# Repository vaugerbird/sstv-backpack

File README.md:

# sstv-backpack
## A ESP32-CAM SSTV backpack for the Baofeng UV-5R and others!

## Project Description
### Turn your HT into a point-and-shoot camera!
This project relies on using an ESP32 connected to a handheld transceiver to send SSTV (Slow Scan TeleVision) images. Any combination of HT and ESP32-CAM can send a picture, but the hardware in this repository is specifically designed to work!

To decode the images, another radio must be used and connected to any device that can run a decoder program. I personally use MMSSTV on my PC with a USB soundcard, or my phone running Robot36 and listening to the radio with the microphone. 

Here's some questions I've been asked in the past:
* **Why?**
    * This is a term project that I created for my college ARC that I'm the president of! We are currently assembling v1.1 and we plan on using the completed projects to do a SSTV scavenger hunt. This consists of a list of things to take pictures of around campus, where the hunter will take a picture of the required object, send the image back to the control room (clubroom), and the point will be awarded to the hunter/team!
* **How does this work?**
    * In short, the ESP32-CAM captures a frame, converts the image into the appropriate encoded audio for SSTV, keys the PTT on the HT, and plays the audio through the microphone port. The specifics of the encoding process are somewhat black magic to me as I didn't create the underlying code, but as far as I understand, the encoding is done by applying a few math functions to the pixels stored in the framebuffer, and converted into audio.

## Hardware Revisions
I currently have 2 hardware revisions available, with a 3rd planned: 
1. v1.0:
    * Mostly through-hole and completely hand-solderable
    * Simplest version with only a voltage regulator circuit, PTT circuit, 2 switches, a buzzer, and the ESP32-CAM
    * Requires external board for flashing and a serial monitor
2. v1.1: 
    * 2 sub-versions:
        * v1.1.1: CH340C version, uses the CH340C for USB-to-UART and has CC resistors for full USB type C compatibility.
        * v1.1.0: FT231XS version, uses the FTDI FT231XS for USB-to-UART and does **not** have CC resistors. I don't recommend this version for many reasons, unless it is difficult to get the CH340C. 
    * Still mostly through-hole and hand-solderable, albeit with some fine-pitch components like the USB-to-UART chip.
    * Retains all the same functionality of v1.0, but adds a USB-to-Serial chip for flashing and a serial monitor.
    * The board is quite cramped and may be hard to work with.
3. v1.2 (WIP):
    * Switch to a mostly top-mounted SMD design, while still being hand-solderable
    * Retain all features of the v1.1 board
    * Maybe add battery charging circuitry?

## Assembly Instructions
### Better (printable) instructions coming soon!
1. Upload your desired [Gerber](./hardware/gerbers/) file to your favorite PCB manufacturer. I recommend OSHPark for US-made, decent-priced priced small-batch PCBs. JLCPCB or PCBWay are both great for cheap, high quality PCBs, if you don't mind waiting.

2. Order the required parts using the proper BOM for [v1.0](./hardware/v1.0/sstv-backpack-v1.0.1.csv) or [v1.1](./hardware/v1.1/sstv-backpack-v1.1.1.csv) from your favorite parts supplier.

3. Once all parts arrive, assemble the board. There isn't much of a technique to it, just start with the lowest profile parts first like the diodes, resistors, and chips, and work your way up.

4. Once the board is complete, print the case using one of the included [STLs](./hardware/case). Currently, the Baofeng UV-5R is the only supported radio, but the Inventor 2025 and STEP files are included, and help with additional radio models is always appreciated!

    * I used the standard settings (0.2mm) on my print, with supports on, and the case interior facing the build plate.

    * The case requires these additional parts:
        * 4 - M3 brass het set inserts
        * 4 - M3 x 6mm screws (preferably hex head)
        * 4 - M2 x 4mm screws
        * 1 - Radio cable (I just cut the end off of a cheap Baofeng speaker-mic, it was cheaper than using an unterminated cable.)

5. After you have the hardware assembled, the next thing to do is upload the code!

## Programming Instructions
1. Ensure that you have this link added to the 3rd party boards section of the Arduino IDE (Found under File -> Preferences -> Additional board manager URLs):
```
https://dl.espressif.com/dl/package_esp32_index.json
```

2. From the board manager, install the newest version of the ESP32 board definitions.

3. Set the board model to "AI Thinker ESP32-CAM" and select the appropriate COM port.

4. Change the text options on lines 37 and 38 of [sstv-backpack.ino](./code/sstv-backpack.ino) to reflect your callsign and desired splash text.
    * The color of the top and bottom text can be changed with the definitions in lines 24-31. 

5. Uncomment line 21 ```#define USE_FLASH``` if you want to use the flash LED (Turns on a high intensity white LED on when framegrabbing).

6. At line 447, set `1 = HIGH` or `0 = LOW` properly reflect your CAPT_BTN wiring (GND for LOW, or +3.3V for HIGH)

7. Between line 452-456, choose the correct button pull-up/pull-down configuration. The button is set to pull-up by default to mirror the PCBs. (Button connects to GND when pressed)

8. Inside the "camera.h" file you can choose between two profiles, DAYLIGHT and HOME. Feel free to modify settings to best suit your case. 
	* Notes from IU5HKU:
		* Keep in mind that this cheap sensor struggles a lot in poor light scenarios, so don't expect a picture like your Fujifilm camera.
		* A quick search online can lead you towards the proper settings values you need.

9. All the board settings can be left alone except for selecting the correct COM port.

10. Upload the code!

## Contributors
 A huge thank you to our contributors for this project! I'm pretty bad with code so all help is greatly appreciated!

 * [IU5HKU / Marco](https://github.com/IU5HKU) - Updated the code to work with the newest version of the ESP32 board definition and improved the readability/usability of the code!
 * [IU5HKU / Marco](https://github.com/IU5HKU) - Updated the code to work with deepsleep/wakeup ESP32 functions (maximize battery life).

## Licensing
* The [main program](./code/sstv-backpack.ino) and [supporting libraries](./code/) are licensed as CC BY-NC-SA 4.0 and are based on the program/libraries from [desafioinventor](https://www.instructables.com/SSTV-Capsule-V2-for-High-Altitude-Balloons/) on Instructables. 
* The case design is roughly based on [this design](https://www.thingiverse.com/thing:5270394) by HStakhiv on [Thingiverse](https://www.thingiverse.com/hstakhiv/designs). The original is licensed under CC BY. My case design falls under the GPL-2.0 license.
* The remaining contents of this repository are designed by me (and contributors!), and are licensed under the GPL-2.0 license.

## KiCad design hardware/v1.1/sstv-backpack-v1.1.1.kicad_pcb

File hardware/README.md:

# Hardware
## Currently there are 3 revisions:
* v1.0(.1)
    * Simplest version
    * The board only acts as a voltage regulator, PTT circuit, and carrier for the major parts
* v1.1
    * More complex
    * The board contains the voltage regulator circuit, USB flashing circuit, and PTT circuit
* v1.2
    * Same complexity as v1.1, contains mostly SMD parts

## HW Issues
* v1.0(.1):
    * This board is incapable of flashing the ESP32 or using serial monitor as there is no USB-to-UART chip present. Flashing has to be done with a dedicated programmer and debugging is very difficult. 
* v1.1.0:
    * ~~No CC resistors are present (or really possible) for the USB-C port. This is due to physical restraints of through-hole components, and means the board will not receive power from a USB-C to USB-C cable.~~ Fixed with v1.1.1
    * ~~Powering the board from the radio and connecting USB data is possible, and won't break anything as power is diode-protected, but is not recommended.~~ Fixed with v1.1.1
* v1.2:
    * No issues have been found; this revision of the board has not yet been tested.

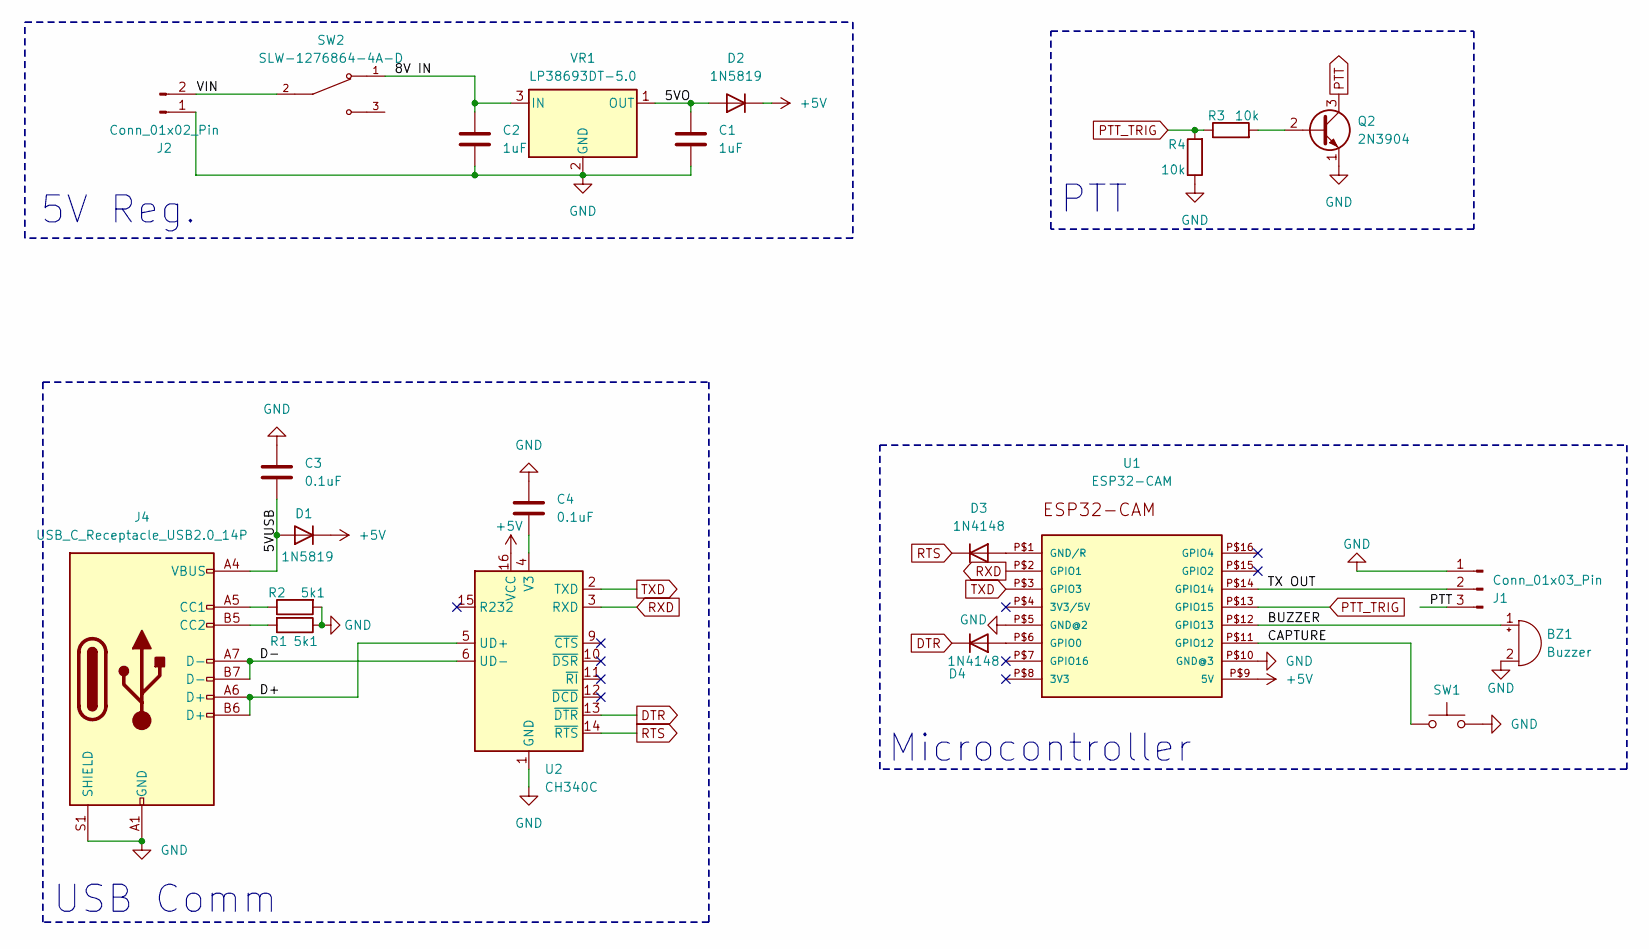
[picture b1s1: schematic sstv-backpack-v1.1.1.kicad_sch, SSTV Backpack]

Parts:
BZ1: Buzzer; Buzzer_TDK_PS1240P02BT_D12.2mm_H6.5mm
C1, C2: 1uF; C_Disc_D3.4mm_W2.1mm_P2.50mm
C3, C4: 0.1uF; C_Disc_D3.4mm_W2.1mm_P2.50mm
D1, D2: 1N5819; D_DO-41_SOD81_P7.62mm_Horizontal
D3, D4: 1N4148; D_DO-41_SOD81_P7.62mm_Horizontal
J1: Conn_01x03_Pin; PinHeader_1x03_P2.54mm_Vertical
J2: Conn_01x02_Pin; PinHeader_1x02_P2.54mm_Vertical
J4: USB_C_Receptacle_USB2.0_14P; USB_C_Receptacle_GCT_USB4085
Q2: 2N3904; TO-92_Inline
R1, R2: 5k1; R_Axial_DIN0207_L6.3mm_D2.5mm_P7.62mm_Horizontal
R3, R4: 10k; R_Axial_DIN0207_L6.3mm_D2.5mm_P7.62mm_Horizontal
SW1: SW_Push
SW2: SLW-1276864-4A-D; SW_SLW-1276864-4A-D; PARTREV 1.01
U1: ESP32-CAM
U2: CH340C; SOIC-16_3.9x9.9mm_P1.27mm
VR1: LP38693DT-5.0; TO-252-2

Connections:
+5V: D1.1 (K), D2.1 (K), U1.P$9 (5V), U2.16 (VCC)
/5VO: C1.1, D2.2 (A), VR1.1 (OUT)
/5VUSB: C3.2, D1.2 (A), J4.A4 (VBUS), J4.A9 (VBUS), J4.B4 (VBUS), J4.B9 (VBUS)
/8V IN: C2.1, SW2.1, VR1.3 (IN)
/BUZZER: BZ1.1 (+), U1.P$12 (GPIO13)
/CAPTURE: SW1.1, U1.P$11 (GPIO12)
/D+: J4.A6 (D+), J4.B6 (D+), U2.5 (UD+)
/D-: J4.A7 (D-), J4.B7 (D-), U2.6 (UD-)
/TX OUT: J1.2, U1.P$14 (GPIO14)
/VIN: J2.2, SW2.2
DTR: D4.1 (K), U2.13 (~DTR)
GND: BZ1.2 (-), C1.2, C2.2, C3.1, C4.1, J1.1, J2.1, J4.A1 (GND), J4.A12 (GND), J4.B1 (GND), J4.B12 (GND), J4.S1 (SHIELD), Q2.1 (E), R1.1, R2.2, R4.1, SW1.2, U1.P$5 (GND@2), U1.P$10 (GND@3), U2.1 (GND), VR1.2 (GND)
unnamed: D3.2 (A), U1.P$1 (GND/R)
unnamed: D4.2 (A), U1.P$6 (GPIO0)
unnamed: J4.A5 (CC1), R2.1
unnamed: J4.B5 (CC2), R1.2
unnamed: Q2.2 (B), R3.2
unnamed: C4.2, U2.4 (V3)
PTT: J1.3, Q2.3 (C)
PTT_TRIG: R3.1, R4.2, U1.P$13 (GPIO15)
RTS: D3.1 (K), U2.14 (~RTS)
RXD: U1.P$2 (GPIO1), U2.3 (RXD)
TXD: U1.P$3 (GPIO3), U2.2 (TXD)

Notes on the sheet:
5V Reg.
Microcontroller
USB Comm
PTT

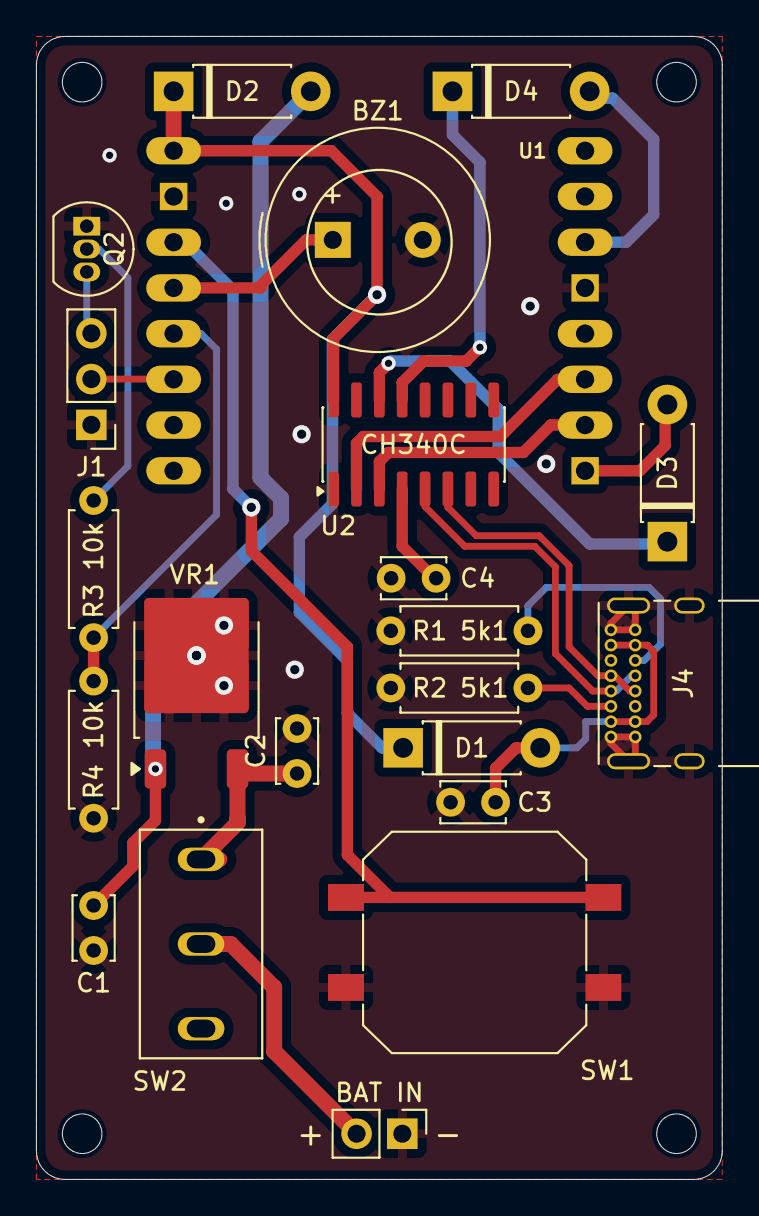
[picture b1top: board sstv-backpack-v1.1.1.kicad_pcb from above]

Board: 2 copper layers, 38.1 x 63.5 mm, 22 parts (0 on the bottom side), 23 nets.

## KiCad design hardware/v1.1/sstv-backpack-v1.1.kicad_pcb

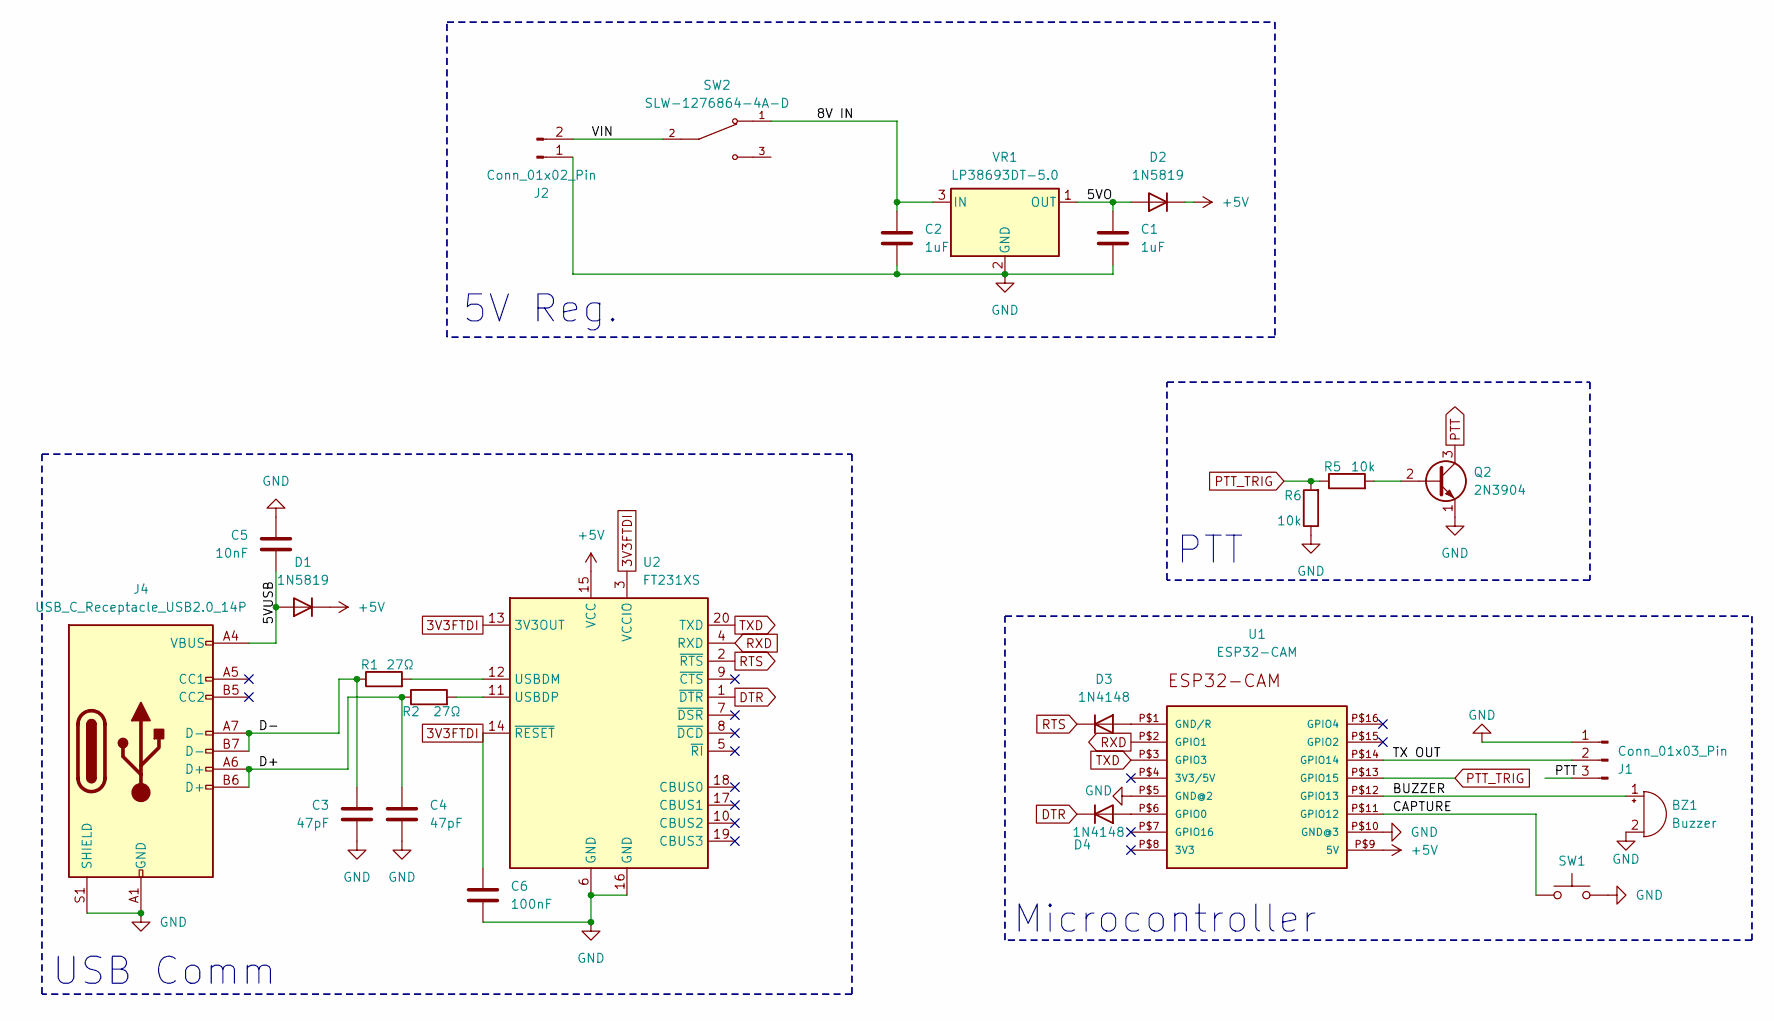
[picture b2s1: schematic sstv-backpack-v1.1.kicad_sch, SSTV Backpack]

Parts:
BZ1: Buzzer; Buzzer_TDK_PS1240P02BT_D12.2mm_H6.5mm
C1, C2: 1uF; C_Disc_D3.4mm_W2.1mm_P2.50mm
C3, C4: 47pF; C_Disc_D4.7mm_W2.5mm_P5.00mm
C5: 10nF; C_Disc_D4.7mm_W2.5mm_P5.00mm
C6: 100nF; C_Disc_D4.7mm_W2.5mm_P5.00mm
D1, D2: 1N5819; D_DO-41_SOD81_P7.62mm_Horizontal
D3, D4: 1N4148; D_DO-41_SOD81_P7.62mm_Horizontal
J1: Conn_01x03_Pin; PinHeader_1x03_P2.54mm_Vertical
J2: Conn_01x02_Pin; PinHeader_1x02_P2.54mm_Vertical
J4: USB_C_Receptacle_USB2.0_14P; USB_C_Receptacle_GCT_USB4085
Q2: 2N3904; TO-92_Inline
R1, R2: 27Ω; R_Axial_DIN0207_L6.3mm_D2.5mm_P7.62mm_Horizontal
R5, R6: 10k; R_Axial_DIN0207_L6.3mm_D2.5mm_P7.62mm_Horizontal
SW1: SW_Push
SW2: SLW-1276864-4A-D; SW_SLW-1276864-4A-D; PARTREV 1.01
U1: ESP32-CAM
U2: FT231XS; SSOP-20_3.9x8.7mm_P0.635mm
VR1: LP38693DT-5.0; TO-252-2

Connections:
3V3FTDI: C6.1, U2.3 (VCCIO), U2.13 (3V3OUT), U2.14 (~RESET)
+5V: D1.1 (K), D2.1 (K), U1.P$9 (5V), U2.15 (VCC)
/5VO: C1.1, D2.2 (A), VR1.1 (OUT)
/5VUSB: C5.2, D1.2 (A), J4.A4 (VBUS), J4.A9 (VBUS), J4.B4 (VBUS), J4.B9 (VBUS)
/8V IN: C2.1, SW2.1, VR1.3 (IN)
/BUZZER: BZ1.1 (+), U1.P$12 (GPIO13)
/CAPTURE: SW1.1, U1.P$11 (GPIO12)
/D+: C4.1, J4.A6 (D+), J4.B6 (D+), R2.1
/D-: C3.1, J4.A7 (D-), J4.B7 (D-), R1.1
/TX OUT: J1.2, U1.P$14 (GPIO14)
/VIN: J2.2, SW2.2
DTR: D4.1 (K), U2.1 (~DTR)
GND: BZ1.2 (-), C1.2, C2.2, C3.2, C4.2, C5.1, C6.2, J1.1, J2.1, J4.A1 (GND), J4.A12 (GND), J4.B1 (GND), J4.B12 (GND), J4.S1 (SHIELD), Q2.1 (E), R6.1, SW1.2, U1.P$5 (GND@2), U1.P$10 (GND@3), U2.6 (GND), U2.16 (GND), VR1.2 (GND)
unnamed: D3.2 (A), U1.P$1 (GND/R)
unnamed: D4.2 (A), U1.P$6 (GPIO0)
unnamed: Q2.2 (B), R5.2
unnamed: R1.2, U2.12 (USBDM)
unnamed: R2.2, U2.11 (USBDP)
PTT: J1.3, Q2.3 (C)
PTT_TRIG: R5.1, R6.2, U1.P$13 (GPIO15)
RTS: D3.1 (K), U2.2 (~RTS)
RXD: U1.P$2 (GPIO1), U2.4 (RXD)
TXD: U1.P$3 (GPIO3), U2.20 (TXD)

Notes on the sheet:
5V Reg.
Microcontroller
USB Comm
PTT

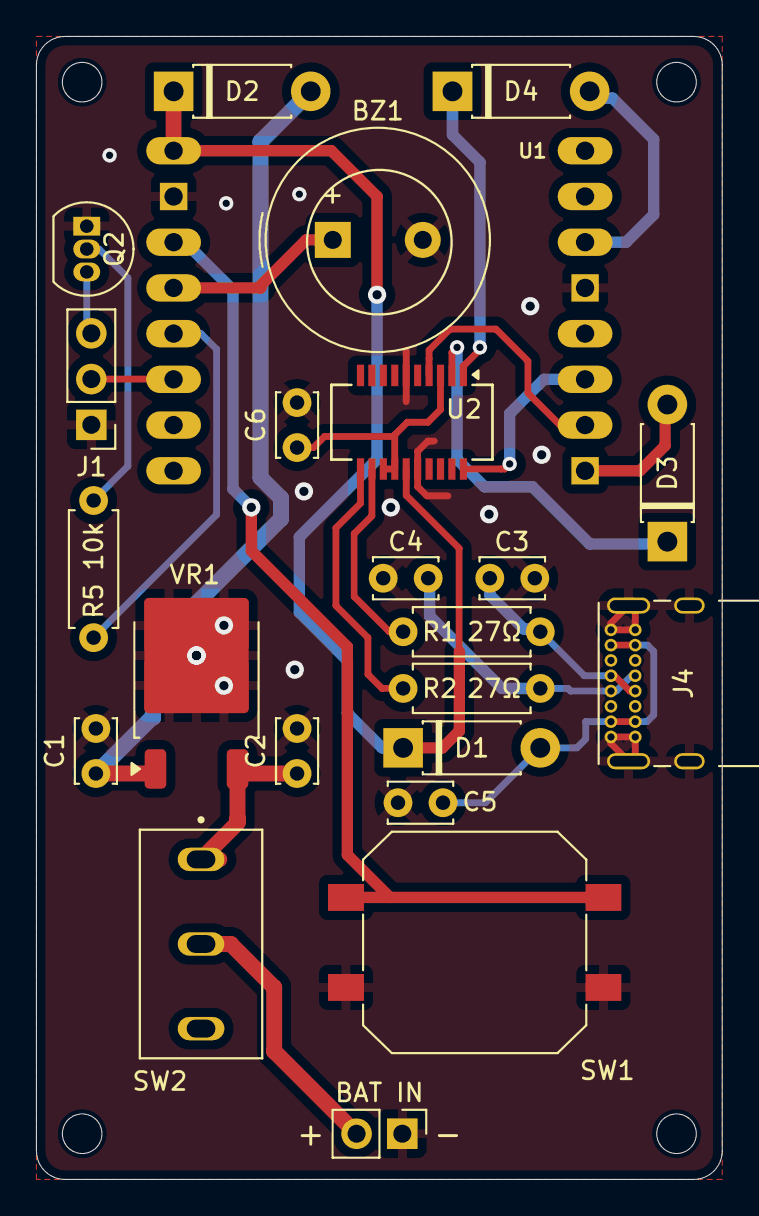
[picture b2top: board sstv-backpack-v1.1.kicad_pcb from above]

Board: 2 copper layers, 38.1 x 63.5 mm, 23 parts (0 on the bottom side), 23 nets.

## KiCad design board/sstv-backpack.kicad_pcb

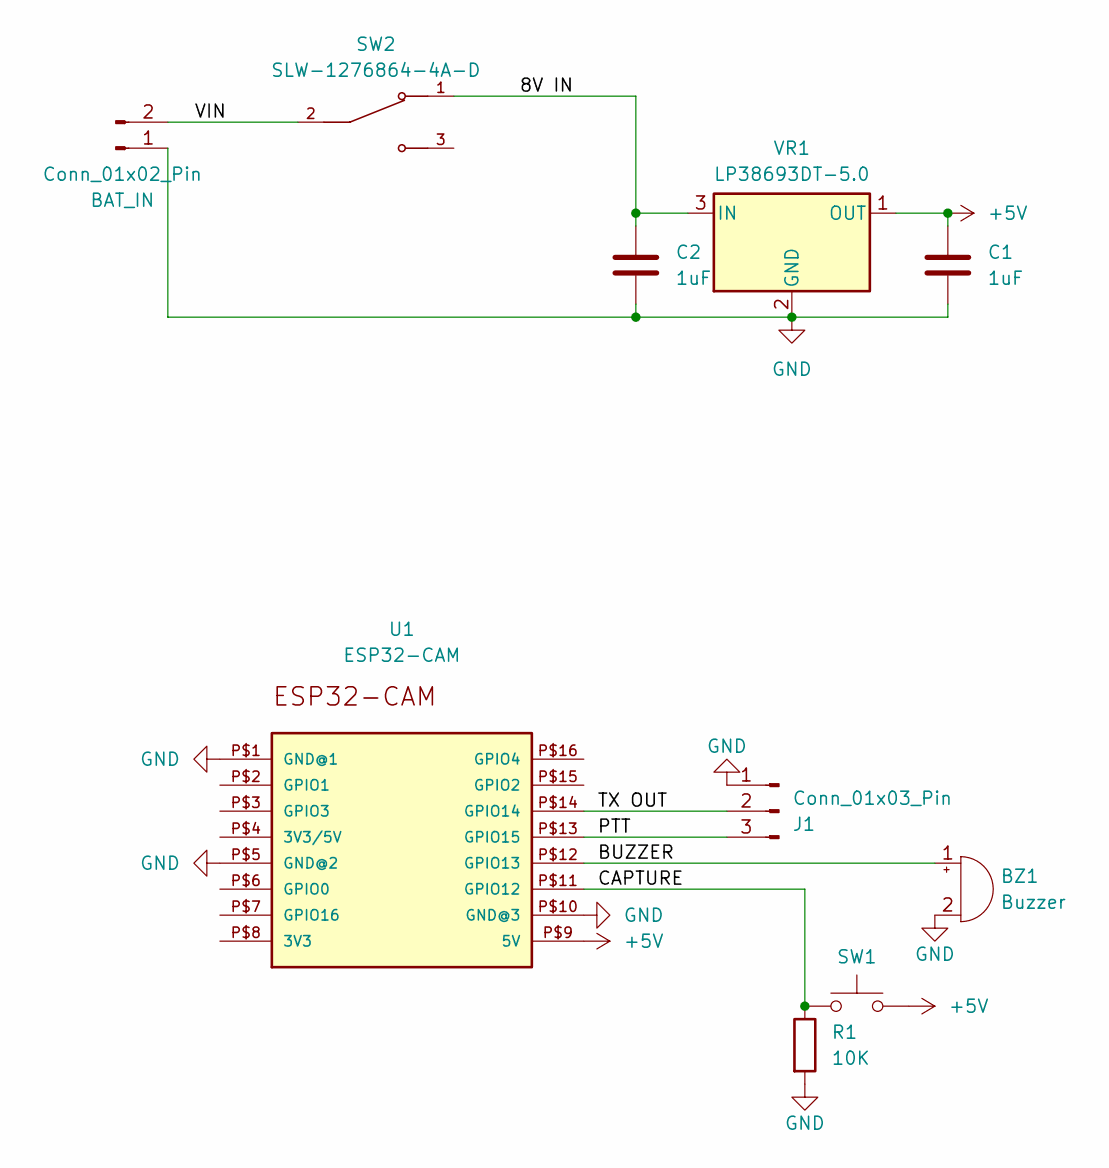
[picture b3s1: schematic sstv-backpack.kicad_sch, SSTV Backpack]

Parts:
BAT_IN: Conn_01x02_Pin; PinHeader_1x02_P2.54mm_Vertical
BZ1: Buzzer; Buzzer_12x9.5RM7.6
C1, C2: 1uF; C_Disc_D4.7mm_W2.5mm_P5.00mm
J1: Conn_01x03_Pin; PinHeader_1x03_P2.54mm_Vertical
R1: 10K; R_Axial_DIN0207_L6.3mm_D2.5mm_P7.62mm_Horizontal
SW1: SW_Push
SW2: SLW-1276864-4A-D; SW_SLW-1276864-4A-D; PARTREV 1.01
U1: ESP32-CAM
VR1: LP38693DT-5.0; TO-252-2

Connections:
+5V: C1.1, SW1.2, U1.P$9 (5V), VR1.1 (OUT)
/8V IN: C2.1, SW2.1, VR1.3 (IN)
/BUZZER: BZ1.1 (+), U1.P$12 (GPIO13)
/CAPTURE: R1.1, SW1.1, U1.P$11 (GPIO12)
/PTT: J1.3, U1.P$13 (GPIO15)
/TX OUT: J1.2, U1.P$14 (GPIO14)
/VIN: BAT_IN.2, SW2.2
GND: BAT_IN.1, BZ1.2 (-), C1.2, C2.2, J1.1, R1.2, U1.P$1 (GND@1), U1.P$5 (GND@2), U1.P$10 (GND@3), VR1.2 (GND)

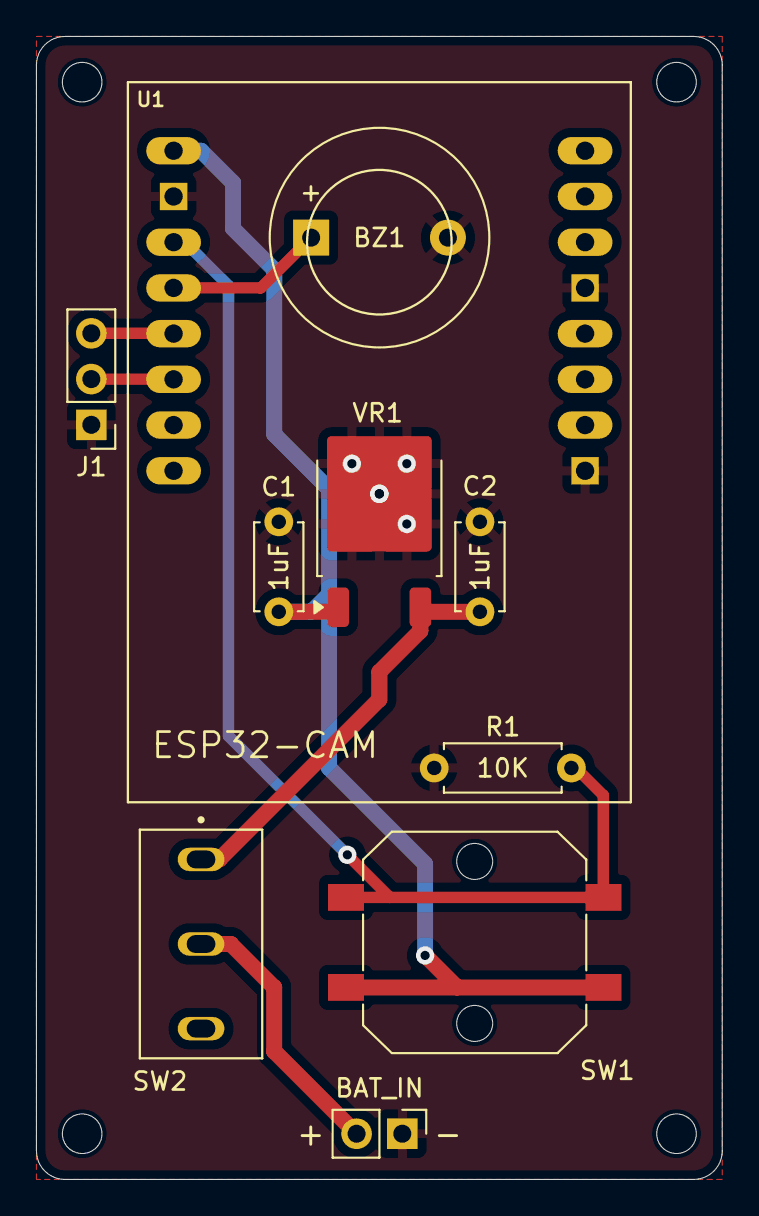
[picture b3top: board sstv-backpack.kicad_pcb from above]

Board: 2 copper layers, 38.1 x 63.5 mm, 10 parts (0 on the bottom side), 8 nets.

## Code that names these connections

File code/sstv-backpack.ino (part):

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#define led_flash 4
#define led_red 33
#define speaker_output 14
#define ptt_pin 15 // Pin for PTT (LOW = GND = active)
#define buzz 13 // Pin for indication buzzer
#define capt_btn 12 // Pin for button to activate capture

int btnState = 0; 
int lastBtnState = 0;
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
  // Activate PTT (LOW = GND)
  Serial.println(" - Activating PTT");
  digitalWrite(ptt_pin, LOW);

  SSTVtime = 0; SSTVnext = 0; SSTVseq = 0; SSTV_RUNNING = true;
  vTaskResume(sampleHandlerHandle);
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
  // Deactivate PTT (HIGH = inactive)
  Serial.println(" - Deactivating PTT");
  digitalWrite(ptt_pin, HIGH);

  esp_camera_fb_return(fb);
  digitalWrite(speaker_output, LOW);
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  pinMode(capt_btn, INPUT_PULLUP);
  pinMode(led_flash, OUTPUT);
  pinMode(led_red, OUTPUT);
  pinMode(ptt_pin, OUTPUT); // Configure PTT as output
  pinMode(buzz, OUTPUT);
  digitalWrite(led_flash, LOW);
  digitalWrite(led_red, HIGH);
  digitalWrite(ptt_pin, HIGH); // PTT inactive at startup

  hw_timer_t *timer = NULL;
  timer = timerBegin(2, 10, true);
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
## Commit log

2025-08-24 Add initial files
2025-08-25 Update silkscreen and gerbers
2025-09-08 Fix v1.0, add v1.1, and restructure
2025-09-09 Fix BOMs and update README
2025-09-21 Swap v1.1 to USB-C and add v1.2
    Swapped v1.1 to USB-C from USB Mini B, added the TX transmit transistor to hopefully fix the TX hang, and added the WIP files for v1.2
2025-09-21 Change callsign in code, update README
2025-09-22 Update v1.1 gerber and BOM
2025-09-22 Restructure code and add license
2025-10-20 Fix PCB and add USB-C to case
2025-10-21 Arduino Core upgrade
    Now compiles with no problems in Arduino Core v3.0.7
2025-10-21 Fix pin naming and update camera settings
    Now you can tweak the sensor parameters as in the "CameraWeb" example
2025-10-21 Revise README for ESP32 setup
    Updated installation instructions and board settings for clarity.
    Now works with ArduinoCore v3.0.7
2025-10-21 Fix SCCB pin names and update camera configurations
    Corrected pin names for SCCB interface and adjusted camera settings.
2025-10-21 Fix typo in SCCB pin configuration
    The only fix needed for your camera.h is this one
2025-10-21 Revise README for ArduinoCore V3.0.7+ compatibility
    Updated README to reflect compatibility with ArduinoCore V3.0.7+ and clarified upgrade notes.
2025-10-21 Fix header formatting in README.md
2025-10-21 Fix pin naming and optimize camera settings
    Optimised camera settings for home and daylight.
    This sensor isn't brillinat in low light, do not expect great results
2025-10-21 Update camera settings in camera.h
    Commented out gain ceiling setting for AGC.
2025-10-21 Revise upgrade notes for ArduinoCore V3.0.7+
    Updated upgrade instructions for ArduinoCore compatibility and improved timer management details.
2025-10-21 Update README with camera profile selection details
    Added information about selecting camera profiles in camera.h.
2025-10-21 Enable gamma correction in camera settings
2025-10-21 Fix SPEAKER_OUT pin name to SPEAKER_OUTPUT
2025-10-22 Stop PWM on LEDC channel 3
    Stop PWM on LEDC channel 3 to silence the pin.
2025-10-22 Refactor camera settings for improved performance
    Camera settings are CRUCIAL if you are using OV2640 sensor (that's an extremely slow one in agc, so carefully tune the parameters before use!!)
2025-10-22 Refactor color definitions for top and bottom strings
    Now you can change top & bottom string color in a more intuitive way
2025-10-22 Update README and code for PTT
2025-10-22 Change file naming for PCBS and add v1.0.1
2025-10-22 Remove temp files and update .gitignore
2025-10-22 Update assembly parts in README
2025-10-23 Update README with clearer camera settings instructions
    Clarify instructions for modifying camera settings in camera.h.
2025-10-24 Refactor audio output handling with ledcWrite
    Now the LEDC code is V3.x.x compliant (use the new APIs)
2025-10-25 Fix definition for SPEAKER_OUTPUT
2025-10-25 Fix text color
2025-10-25 Remove delay after detaching speaker output
    Removed unnecessary delay after detaching speaker output.
2025-10-25 Comment out outdoor settings in camera.h
    Commented out general settings and adjustments for outdoor use in camera.h.
2025-10-27 Update HW README
2025-10-28 Rename SPEAKER_OUT to SPEAKER_OUTPUT
2025-10-28 Refactor sstv-backpack.ino and add deepsleep and wakeup from EXT source
    Refactor code structure and add deepsleep/wakeup functions.
    Now the camera goes in deepsleep when power on, waiting for user input on GPIO_NUM_xx pin for wake up and take a shot.
    In this way you can maximize battery life.
2025-10-28 Enhance README with upgrade notes and contributors
    Added upgrade instructions and contributor updates.
2025-10-28 Fix line number for CAPT_BTN wiring upgrade instruction
    Updated line numbers for CAPT_BTN wiring instructions in README.
2025-10-28 Refactor includes and adjust WiFi handling
    Shutdown WiFi completely
2025-10-29 Add capture tones and make button match
2025-10-29 Update line numbers in README and fix defaults
2025-10-29 Rename v1.0.1 BOM
2025-10-29 Fix BOM links
2025-11-01 Add PTT_PIN hold functionality for deep sleep
    Enable PTT_PIN hold during deep sleep mode.
2025-11-09 Update README and add pull-down resistors for PTT
2025-11-09 Add v1.1.1 with CH340C and update README
2025-11-09 Update hardware README
2025-11-10 Fix some spelling and grammar
2025-11-14 Add STEP file for case
2025-11-21 Create universal case and add Baofeng 5RM
2025-11-21 Update 5RM battery STL
2025-11-22 Add button and switch extension for front case
